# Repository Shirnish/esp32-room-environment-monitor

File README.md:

# ESP32 Room Environment Monitor

I'm building this project as part of my embedded-systems portfolio for Computer Engineering. I started with the Freenove ESP32-S3 kit tutorials and am developing the monitor one version at a time to practice sensor interfacing, debugging, timing, and code organization.

**Current software milestone: V5.1 timed Wi-Fi recovery — October 14, 2026.** I can view temperature, humidity, and motion status from my phone, with the page refreshing every five seconds. The LCD, LEDs, and Serial output still work alongside it. I added a reconnect timer and tested successful recovery twice. I use my router's 2.4 GHz guest network; the original connection rejection is still unexplained, as described in the [Wi-Fi recovery notes](#v51-timed-wi-fi-recovery).

**PCB practice milestone — October 16, 2026:** I also created a routed KiCad carrier-board design. It is an unfabricated layout exercise, separate from the tested breadboard build. [PCB documentation and files](HardWare/room-environment-monitor-v2/ROOM%20ENVIRONMENT%20PCB%20PRACTICE/README.md).

## V1: temperature and humidity over Serial

For V1, I connected a DHT11 sensor and printed temperature in Celsius, temperature in Fahrenheit, and relative humidity to Serial Monitor. I calculate Fahrenheit in the sketch using `(C * 1.8) + 32`.

I use `millis()` to schedule measurement attempts every 2,000 ms. If a reading fails, the program prints the library's error message and waits until the next scheduled attempt before trying again.

I separated the measurement work into `readEnvironment()`. The main `loop()` decides when to call it, while the function reads the sensor, checks its status, calculates Fahrenheit, and prints the results.

## Hardware and wiring

For V1, I used:

- Freenove ESP32-S3 development board and GPIO extension board
- DHT11 temperature/humidity sensor
- 10 kΩ pull-up resistor
- Breadboard, jumper wires, and USB cable

| DHT11 connection | My wiring |
| --- | --- |
| Pin 1: VCC | Board 3.3 V |
| Pin 2: DATA | ESP32-S3 GPIO 21 |
| Pin 3: NC | Unconnected |
| Pin 4: GND | Breadboard ground rail connected to board GND |
| 10 kΩ resistor | Between DATA/GPIO 21 and 3.3 V |

The pull-up resistor holds the data line high when it is idle. Although the tutorial diagram labels the sensor data pin SDA, the DHT11 uses its own digital protocol, not I2C. I don't use an ADC input for this sensor.

Power off before changing wiring, and use the kit's sensor pin diagram to identify the physical pins.

## V1 schematic

[Editable KiCad project](HardWare/room-environment-monitor/room-environment-monitor.kicad_pro) | [PDF schematic](HardWare/room-environment-monitor/room-environment-monitor.pdf)

## Current wiring: V4 schematic

[Editable KiCad project](HardWare/room-environment-monitor-v4/room-environment-monitor-v4.kicad_pro) | [PNG diagram](HardWare/room-environment-monitor-v4/room-environment-monitor-v4.png)

This diagram includes the current GPIO assignments, one 220 ohm resistor per LED, the DHT11 pull-up, the HC-SR501, and the installed LCD voltage interface. V5 adds Wi-Fi and the dashboard without changing the wiring, so this is still the current schematic. I use the module labels to identify connections; the ESP32 board block is a simplified symbol rather than a drawing of the physical headers.

## Software and setup

To run the project:

1. Open `Second_Project.ino` in Arduino IDE. Keep the sketch inside the `Second_Project` folder.
2. Install ESP32 board support, DHTesp, and the kit's LiquidCrystal I2C library. `WiFi` and `WebServer` are included with the ESP32 board package. The LCD communicates through the installed bidirectional level shifter.
3. Copy `secrets.example.h` to `secrets.h` in the sketch folder. Replace the placeholders in `secrets.h` with the name and password of a 2.4 GHz Wi-Fi network. I keep this file local; `.gitignore` excludes it from Git.
4. Select the board configuration and USB port used for the ESP32-S3 kit tutorials.
5. Upload the sketch and open Serial Monitor at **115200 baud**.
6. Check for the startup message, followed by measurements approximately every two seconds. Once Wi-Fi connects, Serial prints `Ip Address:` followed by the assigned address. If it stays disconnected, my retry function prints `Retrying Connection` and starts another attempt when its 30-second interval has elapsed.
7. Connect a phone or computer to the same network and open `http://<printed-IP>/` in a browser, replacing `<printed-IP>` with the actual address. Use HTTP. The page refreshes every five seconds. Guest-network isolation settings can affect whether devices can reach each other; browser access worked on my tested guest network.
8. Allow 60 seconds for PIR warm-up. The backlight stays on and the page says `PIR warming up` during startup. After warm-up, motion and occupancy messages print when their states change, and the backlight follows the occupancy estimate.

Example Serial output:

```text
 Temperature:25.00°C Temperature Fahrenheit:77.00°F Humidity:50.00%
```

This is an example of the output format, not a saved measurement. The installed versions recorded for this milestone are ESP32 board package **3.3.12**, DHTesp **1.19**, and LiquidCrystal I2C **1.1.2**. I still need to record the exact board-menu configuration. The LiquidCrystal I2C library's AVR architecture warning appeared during compilation, but I successfully uploaded and tested the LCD code on my ESP32-S3.

The current sketch runs the DHT11, LCD1602, Serial output, environmental LEDs, PIR motion/occupancy logic, and browser dashboard. I call `readMotion()`, `updateLcdBacklight()`, `checkWifiStatus()`, `wifiConnection()`, and `server.handleClient()` on each loop pass, while `readEnvironment()` stays scheduled every two seconds. The V4 schematic above shows the combined wiring; the earlier schematics remain available as project history.

## V1 testing

I uploaded and tested V1 on my board:

| Test | Result |
| --- | --- |
| Normal sensor readings | Working |
| Celsius, Fahrenheit, and humidity output | Working |
| Refactor into readEnvironment() | Uploaded and working |
| millis() scheduling | Uploaded and working |
| Disconnected DHT11 data wire | Serial printed timeout on the refactored version |

I tested the behavior directly on the hardware. I haven't done sensor accuracy calibration, precise timing measurements, automated build checks, or long-duration testing. I haven't recorded a separate V1 reconnect/recovery test.

To repeat the failure test, power off, disconnect DATA, restart, and check for an error. Power off again before reconnecting DATA, then restart and check that readings return.

## Design decisions and limitations

- I use `millis()` instead of a two-second `delay()` so the program can do other work between measurement attempts.
- I update the attempt timestamp before reading, so failed attempts also respect the interval.
- I use unsigned elapsed-time subtraction to handle millis() rollover.
- I read the sensor inside `readEnvironment()` and save the latest successful measurements in globals for the browser. Opening the page doesn't trigger another sensor read.
- I check the sensor status before converting or printing measurements.
- The sensor transaction still takes time; scheduling with millis() doesn't make the library call asynchronous.
- Printing decimal places doesn't establish the sensor's accuracy or precision.
- I don't store a history of measurements. Failed reads print an error instead of measurements, select the red LED, and replace the LCD readings with an error message. The page hides the saved measurements when `environmentValid` is false, while motion status stays available. The LCD backlight still follows occupancy; sensor errors do not force it on.
- The browser makes a new HTTP request every five seconds. That refresh interval is separate from the two-second sensor interval. Sensor reads, Serial output, I2C operations, and handling a web request can still take time.
- I check Wi-Fi retry timing with `millis()` instead of waiting in a connection loop. My scheduled retry attempts are at least 30 seconds apart. The ESP32 library may also make its own automatic connection attempts.

## V2: LCD development and voltage investigation

I added an I2C LCD1602 while keeping the Serial output. I tested Celsius and Fahrenheit on the first row, humidity on the second, and the messages "Sensor error" and "Check Wiring" when the DHT11 reading fails. My error handler clears both rows before printing its messages. I still need to add padding to normal measurement updates so shorter values fully replace previous text.

I used address **0x27**, SDA on **GPIO 14**, and SCL on **GPIO 13**. Following the Freenove tutorial, I initially powered the LCD from the extension board's USB-supplied **5 V** and connected it to the board's GND.

### V2 schematic: previously tested direct wiring

[Editable V2 direct-wiring KiCad project](HardWare/room-environment-monitor-v2-current/room-environment-monitor-v2-current.kicad_pro) | [PNG diagram](HardWare/room-environment-monitor-v2-current/room-environment-monitor-v2-current.png)

This diagram records the direct 5 V LCD connection I used during functional testing, without a level shifter. I measured the disconnected LCD signal pins near 5 V afterward, so I am documenting this circuit with its unresolved voltage issue rather than treating it as electrically validated. The separate V2 design below shows the level-shifting approach; the current combined V4 schematic is linked above.

### Earlier V2 level-shifter design

[Editable V2 KiCad project](HardWare/room-environment-monitor-v2/room-environment-monitor-v2.kicad_pro) | [PNG diagram](HardWare/room-environment-monitor-v2/room-environment-monitor-v2.png)

I created this diagram while planning the LCD voltage-interface correction. I have since installed the shifter and added the LEDs and PIR. This earlier sheet does not include those additions; the current V4 schematic above documents the combined build.

### Voltage measurements

With the LCD powered at 5 V and its SDA/SCL wires disconnected from the ESP32, I measured approximately **4.9-5.0 V** on those signals relative to GND. I then tried powering the LCD from 3.3 V. The signals measured approximately **3.3 V**, but the display did not show text.

I'm still learning to use the multimeter, so measurement error is possible. I haven't independently verified the readings or checked the meter's accuracy. However, the voltage change followed the module's supply voltage, which is consistent with pull-up resistors connected to that supply. I can't assume the readings are harmless or dismiss them as an error without further testing.

The [ESP32-S3 datasheet, Table 5-4](https://documentation.espressif.com/esp32-s3_datasheet_en.pdf) specifies a high-level input maximum of VDD + 0.3 V, approximately **3.6 V** with a 3.3 V GPIO supply. My measured 5 V signals exceed that specification. Seeing the display work doesn't confirm that the direct connection is electrically compatible.

### Installed LCD interface — October 11, 2026

I installed one module from the [DIYables five-pack of presoldered four-channel bidirectional I2C level shifters](https://diyables.io/products/5-pack-4-channel-iic-i2c-level-converter-module-bi-directional-logic-level-shifter-5v-to-3.3v-for-arduino-raspberry-pi-esp8266-esp32-sensors-presoldered-compact-adapter-board). It translates SDA and SCL between the ESP32's 3.3 V side and the LCD's 5 V side. The LCD still takes power directly from the extension board's USB-supplied 5 V; the shifter does not generate its power.

| Connection | My wiring |
| --- | --- |
| Shifter LV | Board 3.3 V |
| Shifter HV | Board 5 V |
| Shifter GND connections | Board GND |
| LV1 | GPIO 14 / SDA |
| HV1 | LCD SDA |
| LV2 | GPIO 13 / SCL |
| HV2 | LCD SCL |
| LCD VCC | Board 5 V, shared with shifter HV |
| LCD GND | Board GND, shared with all modules |

Channels 3 and 4 are unused. I disconnected USB while changing wiring. Before connecting LV1/LV2 to the ESP32 GPIOs, I powered the shifter and LCD with LCD communication disabled and checked DC voltages relative to common GND:

| Signal | Approximate idle measurement |
| --- | --- |
| LV1 | 3.3 V |
| LV2 | 3.3 V |
| HV1 | 5 V |
| HV2 | 5 V |

I then restored the GPIO connections, LCD initialization, normal measurement display, and sensor-error display calls. The LCD worked alongside Serial output, environmental LEDs, and PIR reporting. With DHT11 DATA disconnected and the board restarted, the LCD showed "Sensor error" / "Check Wiring", the red LED was on, and Serial reported the sensor error. PIR reporting still worked after warm-up. After reconnecting DATA and restarting, normal readings and the appropriate environmental LED returned.

These were manual functional tests and idle DC measurements. I haven't recorded I2C waveforms, independently calibrated the meter, or tested long-duration bus operation. The recovery test used a restart; it does not establish recovery without restarting. I performed these combined sensor-error and recovery tests before adding the backlight control described in V4 below.

The current temperature-row layout is intended for readings below **100 °F**. Higher readings need a shorter layout to fit within the LCD's 16 columns.

## V3: environmental LED status indicators

For this milestone, I added green, yellow, and red LEDs while keeping the DHT11 readings and Serial output. Each LED has its own 220 ohm series resistor. I tested the LEDs individually before connecting their behavior to the sensor readings.

### LED wiring

| LED | ESP32-S3 GPIO | Connection |
| --- | --- | --- |
| Green | 4 | GPIO 4 -> 220 ohm resistor -> anode; cathode -> GND |
| Yellow | 5 | GPIO 5 -> 220 ohm resistor -> anode; cathode -> GND |
| Red | 6 | GPIO 6 -> 220 ohm resistor -> anode; cathode -> GND |

The LEDs and DHT11 share the board's GND. My DHT11 wiring remains the same as V1. I removed the LCD during the original V3 tests; it is now restored in the combined V4 build.

### Status logic

I set the temperature limits to **20-26 degrees Celsius** and the humidity limits to **30-60% relative humidity**. Both endpoints count as within range. These are adjustable project thresholds, not a calibrated assessment of room conditions.

| Sensor result | Green | Yellow | Red |
| --- | --- | --- | --- |
| Valid reading; both measurements within range | ON | OFF | OFF |
| Valid reading; either measurement outside range | OFF | ON | OFF |
| Failed reading | OFF | OFF | ON |

All three LEDs start off until the first measurement attempt. I check the sensor status before comparing measurements, so a failed read selects red instead of being treated as an environmental warning.

I moved the repeated LED writes into `ledControl(bool greenOn, bool yellowOn, bool redOn)`. Its parameters are ordered green, yellow, red. Each status call sets all three outputs, so an LED from the previous status doesn't stay on. `readEnvironment()` still handles the sensor check and range decisions, while `loop()` schedules measurement attempts with `millis()`.

### Hardware testing

I uploaded the sketch and tested these behaviors on my ESP32-S3:

| Test | Result |
| --- | --- |
| Green, yellow, and red LEDs tested individually | Each LED worked; Serial readings continued |
| Within-range reading | Green only |
| Reading outside either configured range | Yellow only |
| Disconnected DHT11 DATA | Red only, with the sensor error in Serial |
| DATA reconnected and board restarted | Normal readings and the appropriate valid-reading indicator returned |
| Refactor into ledControl() | Uploaded and repeated the green, yellow, and red tests successfully |

During testing, a reading of **22.9 degrees Celsius and 64% humidity** selected yellow because humidity exceeded 60%. I temporarily raised `maxHumidity` to 70 to test green, then restored it to 60. Changing the limit let me test the decision without replacing the sensor's measurements with made-up values.

These are manual functional tests. I haven't tested every exact threshold boundary, millis() rollover on hardware, sensor accuracy, or long-duration operation. There is no hysteresis yet, so readings that cross a threshold repeatedly can switch between green and yellow. Reconnecting DATA with a restart verifies recovery after restart; it doesn't establish recovery without restarting.

### Build photos

My ESP32-S3, DHT11, and three status LEDs during V3 testing. The yellow status LED is lit; I had removed the LCD while its level-shifter integration was pending.

A second view of the physical breadboard build. The photos document the assembly; the wiring tables record the GPIO assignments and resistor values.

The LED milestone is complete. I later restored the LCD through the level shifter and tested it with the LEDs and PIR, as recorded in the October 11 integration above.

## V4: PIR motion and occupancy estimate

I added the kit's HC-SR501 PIR motion sensor while keeping the DHT11, Serial output, and environmental LEDs working. I first developed this version with the LCD removed, then restored the display through the level shifter and added occupancy-controlled backlight behavior.

### PIR wiring

| HC-SR501 connection | My wiring |
| --- | --- |
| VCC / + | Extension board's USB-supplied 5 V |
| OUT / S | ESP32-S3 GPIO 7 |
| GND / - | Board GND, shared with the DHT11 and LEDs |

I identify the module pins from their labels and the kit diagram, rather than assuming a left-to-right order. The module uses 5 V power and provides an approximately 3.3 V HIGH output, as described in [Freenove's HC-SR501 documentation](https://docs.freenove.com/projects/fnk0082/en/latest/fnk0082/codes/Python/25_Infrared_Motion_Sensor.html). I read OUT with `digitalRead()`; the PIR needs no additional library or ADC conversion.

### Timing and state logic

| Setting | Current value | Purpose |
| --- | --- | --- |
| `readInterval` | 2,000 ms | Schedule DHT11 measurement attempts |
| `pirWarmupInterval` | 60,000 ms | Suppress PIR and occupancy reporting during startup |
| `occupancyTimeout` | 15,000 ms | Keep the occupancy estimate true after the last sampled HIGH |

I set `pirStartTime` in `setup()`. During warm-up, `readMotion()` returns immediately, so temperature, humidity, and LED updates continue without a 60-second `delay()`.

I call `readMotion()` on each pass through `loop()`, outside the two-second DHT timing condition. Motion polling is independent of that interval, although a sensor transaction or Serial output can still take time. This is polling, not interrupt-based event capture.

`previousMotionState` starts at -1 so the first PIR reading after warm-up prints once. Later, I print `PIR: 0` or `PIR: 1` only when the level changes.

When the PIR is HIGH, I set `occupied` to true and refresh `lastMotionTime` on every HIGH reading. When it is LOW, I keep the previous occupancy estimate until 15 seconds have elapsed since the last sampled HIGH. New HIGH readings refresh the timer. I capture the old occupancy value before updating it, then print an occupancy message only if the value changed.

An illustrative sequence of motion messages is:

```text
PIR: 1
Occupancy: Occupied
PIR: 0
Occupancy: No Recent Movement
```

The last line appears after the software timeout; it is not printed immediately with `PIR: 0`. Temperature and humidity messages continue between these events. This example shows the format, not a captured Serial log. If the first PIR reading is LOW, only `PIR: 0` prints initially because `occupied` already starts false.

### Hardware testing

I uploaded and tested the motion and occupancy behavior on my ESP32-S3:

| Test | Result |
| --- | --- |
| PIR motion and return to LOW | Both 1 and 0 observed |
| `readMotion()` refactor and motion-change reporting | Working; PIR messages print on level changes |
| 60-second warm-up | Environmental readings and LEDs continue; PIR reporting begins after warm-up |
| HIGH after warm-up | Occupancy becomes true and prints once |
| LOW before the software timeout | Occupancy stays true |
| LOW through the 15-second software timeout | Occupancy clears and prints once |
| HIGH returns before the timeout expires | Timer refreshes and occupancy stays true |

During the earlier raw-input test, I estimated that the PIR took about 40-60 seconds to return LOW after activity. I did not time that precisely. The module's own hold time and my software timeout are separate: the software keeps occupancy true for about 15 seconds after the output goes LOW. I haven't recorded the potentiometer positions or H/L jumper setting yet.

### Occupancy-controlled LCD backlight

I added `updateLcdBacklight()` and call it immediately after `readMotion()`. The backlight starts on and stays on during the 60-second PIR warm-up. After warm-up, it follows `occupied`: recent activity turns it on, and the occupancy timeout turns it off. If the first PIR reading after warm-up is LOW and no activity has been recorded, it turns off at that point.

I track the commanded backlight state in `lcdBacklightOn` and send `lcd.backlight()` or `lcd.noBacklight()` only when the desired state changes. Turning off the backlight leaves the LCD powered. Measurement display updates, Serial output, environmental LEDs, and motion polling continue.

I uploaded this version and tested:

| Test | Result |
| --- | --- |
| Startup warm-up | Backlight stays on |
| LOW after warm-up with no recorded activity | Backlight turns off |
| PIR HIGH / occupied | Backlight turns on |
| PIR returns LOW | Backlight remains on during the occupancy grace period |
| LOW continues through the occupancy timeout | Backlight turns off |
| Backlight off | Serial readings and environmental LEDs continue working |

The backlight follows occupancy even during a DHT11 error. Error text is still written to the LCD, but the code does not force illumination on; Serial and the red LED remain the other error indicators. The final hardware photos below show normal operation and the LCD/red-LED response to a disconnected DHT data wire on the current build.

### Current build photos

My combined V4 assembly with the PIR held above the breadboard and the LCD connected alongside it. The breadboard includes the DHT11, level shifter, and three environmental status LEDs.

A closer view of my DHT11, installed level shifter, and LED wiring. These photos document the physical assembly; they do not show active LCD readings. My functional test results are recorded in the tables above.

### Limitations and next steps

This is an occupancy estimate based on recent PIR activity. A stationary person may stop triggering the sensor, so I use the message "No Recent Movement" instead of claiming that the room is empty. A LOW reading also doesn't distinguish no activity from a disconnected or failed PIR signal.

These are manual functional tests. I haven't measured response latency, checked long-duration operation or millis() rollover on hardware, or calibrated detection coverage. PIR reporting is suppressed during warm-up, so startup should not be interpreted as a confirmed empty-room state.

The combined V4 motion/occupancy, LCD, and backlight milestone is complete. The updated KiCad diagram above includes the PIR, LEDs, and installed level shifter. The current build photos are included above, and the earlier V3 photos remain labeled as V3.

## V5: Wi-Fi and browser dashboard

I started by connecting the ESP32 to Wi-Fi and printing its IP address in Serial Monitor. I then added a simple web response and opened it on my phone. Once that worked, I added the readings, sensor-error handling, motion status, an HTML heading, and automatic refresh.

My V5 dashboard displaying 22.0 C, 71.6 F, 64.2% humidity, and an occupied status. This image records the page during testing; the values come from the saved sensor readings and motion state.

The page currently shows:

- Temperature in Celsius and Fahrenheit
- Relative humidity
- `Sensor Reading Unavailable` if the DHT reading fails or no successful reading has happened yet
- `PIR warming up`, `Occupancy: Occupied`, or `Occupancy: No recent Movement`

The ESP32 serves the page at `/` on port 80. I build the response in `handleRoot()` and send it once with `server.send()`. The page uses a five-second HTML refresh setting, so I don't need to reload it manually.

### Saved readings and separate state

I keep the latest successful measurements in `latestTemperatureC`, `latestTemperatureF`, and `latestHumidity`. `environmentValid` starts false, becomes true after a successful read, and goes false after a failed read. The saved numbers remain in memory after a failure, but the page shows the error message instead of presenting them as current readings.

The browser uses these saved values. `readEnvironment()` still controls when the DHT is read, so opening or refreshing the page doesn't request another measurement. I add motion status separately from the environmental `if/else`, so a DHT error doesn't hide occupancy information. During PIR warm-up, I show the warm-up message instead of treating the initial false occupancy value as no recent movement.

### What I tested

I uploaded each addition and checked it on my ESP32-S3 and phone:

| Test | Result |
| --- | --- |
| Connect to the 2.4 GHz guest network | Connected and received an IP address |
| Open the printed HTTP address on my phone | Displayed `Room Monitor Online` in the first test |
| Add the saved Celsius, Fahrenheit, and humidity readings | Displayed the measurements |
| Failed DHT reading | Page displayed the unavailable message |
| Add PIR warm-up and occupancy reporting | Page displayed motion status separately from the measurements |
| Convert the response to HTML | Heading and measurement lines displayed correctly |
| Add the five-second refresh setting | Page refreshed without manually reloading |

These were manual functional tests. I haven't measured request latency, tested multiple browsers at once, or run a long-duration test. The V5.1 section below records the reconnect changes and two successful recovery tests.

### Wi-Fi connection investigation

I tested with a NETGEAR Nighthawk RAX50. Attempts on my main network reported reason `201` (`NO_AP_FOUND`). Separating the 2.4 GHz network from Smart Connect didn't resolve it. Using the 2.4 GHz guest network did let the ESP32 connect, and I could access the page from my phone.

During reset and USB disconnect/reconnect testing, some connection attempts failed. Serial showed `Association refused too many times, max allowed 1`, reason `208` (`ASSOC_COMEBACK_TIME_TOO_LONG`), and reason `36` (`STA_LEAVING`). I haven't confirmed the cause. The [Espressif reason-code documentation](https://docs.espressif.com/projects/esp-idf/en/stable/esp32s3/api-guides/wifi-driver/station-scenarios.html) describes reason 208 as an association response with a comeback time that is too long.

I kept the disconnect callback to print the reason codes. My application starts the initial connection in `setup()` and reports connection changes in `checkWifiStatus()`. I then added the timed retry function below to recover from failures instead of relying on another manual reset.

## V5.1: timed Wi-Fi recovery

I added `wifiConnection()` and call it from `loop()`, outside the two-second sensor timing block. It checks whether Wi-Fi is disconnected and whether at least `wifiRetryInterval` (30,000 ms) has passed since my previous attempt. If both are true, it updates `lastWifiAttemptTime`, prints `Retrying Connection`, and calls `WiFi.reconnect()`.

I set the timestamp before the first `WiFi.begin()` call too. Updating it before each retry keeps unsuccessful attempts from being repeated on every loop pass. The function has no waiting loop or `delay()`. `WiFi.reconnect()` starts an attempt; `checkWifiStatus()` reports the IP and starts the web server when a connection is established.

| Test | Result |
| --- | --- |
| New timed reconnect code | ESP32 reconnected successfully in two manual tests |

The two successful recoveries show that the new retry code can recover in my tested setup. I haven't recorded recovery times, the reason code for each test, a larger reset test series, or a separate network-outage recovery test. The original association rejection is still unexplained, so I am documenting recovery rather than claiming that the underlying router issue is fixed.

## Final hardware demonstration

I used photos to document the finished breadboard build alongside the dashboard image above.

The LCD shows 22.2 C, 72.0 F, and 65.8% humidity. Temperature is within my configured 20-26 C range, but humidity is above the 60% upper limit, so the yellow LED is on. The reading is valid; yellow means a measurement is outside my project limits.

I disconnected the DHT data wire to test a failed reading. The LCD shows `Sensor error` and `Check Wiring`, and the red LED is on. This is the sensor-failure state, separate from the yellow environmental warning.

| Photo | What I demonstrated |
| --- | --- |
| Normal readings with yellow LED | Valid measurements, with humidity outside the configured range |
| DHT DATA disconnected with red LED | Failed sensor reading and LCD error message |

These photos record the LCD and LED states. The dashboard image and manual test results are documented separately above.

### Remaining breadboard improvements

This completes the planned breadboard build and its photo documentation. I also used the circuit as the basis for the separate PCB practice exercise below. The breadboard tests do not establish that the PCB works.

Other possible improvements are investigating the original Wi-Fi rejection, a phone-friendly page layout, and padding normal LCD updates so shorter readings clear the previous text.

## PCB practice: KiCad carrier board

I made a two-layer carrier-board layout to practice schematic-to-PCB work in KiCad. It uses the Freenove ESP32-S3 development board directly in two socket rows, without the GPIO extension board. The DHT11, LED resistors, level-shifter sockets, and external LCD/PIR connectors follow the room monitor's signal assignments.

**This is an unfabricated design exercise.** I have not ordered, assembled, or tested this PCB. The plug-in ESP32 and level-shifter modules are represented by sockets in the rendering; the generic LED models all appear red.

Fresh checks in KiCad CLI **10.0.6 on October 16, 2026** reported **0 ERC errors/warnings, 0 DRC errors/warnings, 0 unconnected PCB items, and 0 schematic-parity issues**, under the saved project's enabled checks. Module fit and the provisional level-shifter row spacing remain unverified.

[PCB design notes, pin mapping, limitations, and editable files](HardWare/room-environment-monitor-v2/ROOM%20ENVIRONMENT%20PCB%20PRACTICE/README.md) · [PCB layout screenshot](docs/images/pcb-practice/pcb-layout.png) · [Schematic screenshot](docs/images/pcb-practice/schematic.png)

The PCB notes explain the front ground pour, routing on both copper layers, the LCD-ground thermal-relief correction, dimension sources, and the guided workflow. They also link the fresh check reports and input hashes.

## Version progression

- **V1:** DHT11 to Serial Monitor — completed and hardware tested as described above
- **V2:** LCD1602 output — restored through the level shifter; idle voltages and combined functional tests recorded above
- **V3:** Environmental LED status indicators — completed and hardware tested; working with the restored LCD
- **V4:** PIR motion/occupancy estimate and LCD backlight control — completed and hardware tested as described above
- **V5:** Wi-Fi and a browser dashboard — dashboard tested on my phone
- **V5.1:** Timed Wi-Fi recovery — reconnected successfully in two manual tests; original rejection cause remains unconfirmed

V5 and V5.1 use the V4 wiring and assembly photos above. The V5 dashboard image and final LCD/LED demonstration photos document the working breadboard build. The separate PCB practice design is routed and checked in KiCad, but has not been fabricated or hardware tested.

## References and attribution

I used the **Freenove ESP32-S3 Ultimate Starter Kit tutorial** as the starting point for the sensor code and wiring. The tutorial schematic was a reference; I haven't redistributed it in this repository.

My changes include calculating Fahrenheit, replacing the goto retry loop with error reporting, using millis() scheduling, separating the work into functions, adding LCD measurements and error messages, selecting LED status indicators from sensor validity and configurable thresholds, adding PIR state-change reporting with a non-blocking warm-up and occupancy timeout, installing I2C level shifting, controlling the LCD backlight from the occupancy estimate, serving saved readings and motion status in a browser, and adding timed Wi-Fi retries.

Libraries:

- [DHTesp](https://github.com/beegee-tokyo/DHTesp)
- [LiquidCrystal I2C](https://github.com/marcoschwartz/LiquidCrystal_I2C)
- [Arduino-ESP32](https://github.com/espressif/arduino-esp32) — board support, WiFi, and WebServer

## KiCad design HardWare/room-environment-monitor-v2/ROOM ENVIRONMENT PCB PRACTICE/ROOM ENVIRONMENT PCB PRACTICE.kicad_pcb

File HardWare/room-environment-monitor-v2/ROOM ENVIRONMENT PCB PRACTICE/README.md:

# Room Monitor — KiCad PCB Practice

I made this carrier-board layout to practice moving from a schematic to a routed PCB in KiCad. It uses the DHT11, LEDs, PIR connector, LCD connector, and I2C level-shifter interface from my room monitor.

**Status — October 16, 2026:** schematic and PCB checks pass under the saved project settings. This is an **unfabricated design exercise**. I have not ordered, assembled, powered, or physically tested this PCB. The working breadboard build and its tests are documented in the [main project README](../../../README.md).

This is a KiCad rendering, not a photograph of an assembled PCB. The ESP32-S3 and level-shifter modules are represented by their sockets. The LCD and PIR are external modules connected through J1 and J2. All three LEDs look red because they share a generic 3D model; the schematic and silkscreen identify their intended colors.

## Project files

Open [ROOM ENVIRONMENT PCB PRACTICE.kicad_pro](<ROOM ENVIRONMENT PCB PRACTICE.kicad_pro>) in **KiCad 10.0.6**, then open its schematic or PCB. Keep the following files together:

| File | Purpose |
| --- | --- |
| [Schematic](<ROOM ENVIRONMENT PCB PRACTICE.kicad_sch>) | Connections and assigned footprints |
| [PCB layout](<ROOM ENVIRONMENT PCB PRACTICE.kicad_pcb>) | Placement, routing, outline, ground zone, and silkscreen |
| [Project settings](<ROOM ENVIRONMENT PCB PRACTICE.kicad_pro>) | Saved rules and project configuration |
| [RoomMonitor.kicad_sym](RoomMonitor.kicad_sym) and [sym-lib-table](sym-lib-table) | Local symbols and their project-relative library registration |
| [ERC report](ERC.rpt) / [ERC JSON](validation/erc.json) | Fresh schematic-check results |
| [DRC report](validation/DRC.rpt) / [DRC JSON](validation/drc.json) | PCB-check, connectivity, and schematic-parity results |
| [Validation manifest](validation/manifest.json) | Check date, options, and SHA-256 hashes of the checked inputs, with text line endings normalized to LF |

The footprints use KiCad's standard libraries. Install the standard symbol and footprint libraries when opening the project on another computer; the 3D models also depend on the corresponding KiCad model libraries. The folder is under `room-environment-monitor-v2` for historical reasons; this practice layout includes the later LEDs, PIR, and level-shifted LCD connections.

## What the board represents

| Reference | Part or connection |
| --- | --- |
| J5 / J6 | Two 20-position sockets for the Freenove ESP32-S3 development board, used directly without its GPIO extension board |
| U2 / R4 | Bare four-pin DHT11 and its 10 kΩ data pull-up to 3.3 V |
| D3 / R1 | Green LED and 220 Ω series resistor, controlled by GPIO4 |
| D2 / R2 | Yellow LED and 220 Ω series resistor, controlled by GPIO5 |
| D1 / R3 | Red LED and 220 Ω series resistor, controlled by GPIO6 |
| J2 | Three-pin cable connector for the HC-SR501 PIR, with OUT connected to GPIO7 |
| J3 / J4 | The LV and HV socket rows of one plug-in, four-channel level-shifter module |
| J1 | Four-pin cable connector for the external I2C LCD1602 |

This carrier assumes the ESP32 development board provides USB-derived 5 V and regulated 3.3 V through its headers. I did not add a separate USB connector, regulator, or power-selection circuit to the carrier.

### Connector pin order

These orders refer to the **top view of this PCB**, matching the silkscreen. J2 is rotated, so its numbering runs in the opposite direction from J1.

| Connector | Top-to-bottom pad numbers | Top-to-bottom signals |
| --- | --- | --- |
| J1 — LCD | 1, 2, 3, 4 | GND, 5 V, SDA, SCL |
| J2 — PIR | 3, 2, 1 | GND, OUT, 5 V |
| J3 — LV | 1, 2, 3, 4, 5, 6 | LV1/SDA, LV2/SCL, 3.3 V, GND, LV3 unused, LV4 unused |
| J4 — HV | 1, 2, 3, 4, 5, 6 | HV1/SDA, HV2/SCL, 5 V, GND, HV3 unused, HV4 unused |

The cable wiring must match the actual LCD and PIR module labels. These connector orders are the carrier's assignments, not a claim that every module sold with the same name has the same physical pin order.

### Signal and voltage connections

| Function | PCB connection |
| --- | --- |
| DHT11 data | U2 pin 2 and R4 pin 2 → J6 pin 17 / GPIO21 |
| DHT11 supply | U2 pin 1 and R4 pin 1 → 3.3 V |
| DHT11 unused pin | U2 pin 3 remains unconnected |
| Green / yellow / red control | R1 / R2 / R3 pin 1 → J5 pins 3 / 4 / 5, respectively |
| PIR OUT | J2 pin 2 → J5 pin 6 / GPIO7 |
| I2C SDA, low-voltage side | J5 pin 19 / GPIO14 → J3 pin 1 |
| I2C SCL, low-voltage side | J5 pin 18 / GPIO13 → J3 pin 2 |
| I2C SDA, high-voltage side | J4 pin 1 → J1 pin 3 |
| I2C SCL, high-voltage side | J4 pin 2 → J1 pin 4 |
| 3.3 V distribution | J5 pin 1 → J3 pin 3, U2 pin 1, and R4 pin 1 |
| 5 V distribution | J5 pin 20 → J2 pin 1, J4 pin 3, and J1 pin 2 |
| Common ground | J6 pin 20, U2 pin 4, LED cathodes, J1 pin 1, J2 pin 3, and J3/J4 pin 4 |

The level-shifter module translates SDA and SCL internally. I did not route a direct copper connection between its LV and HV signal pins. Its HV reference and the LCD supply use 5 V; its LV reference and the ESP32 GPIO side use 3.3 V.

## Schematic and layout

[Zoomable schematic SVG export](../../../docs/images/pcb-practice/schematic.svg)

The schematic represents the two physical ESP32 header rows, while the earlier V4 wiring diagram in the main README uses a simplified board block. `PWR_FLAG` symbols tell ERC which power nets have a source; they do not create a supply or regulate voltage.

The saved layout has **two copper layers, 14 footprints, 77 pads, 64 track segments, no vias, and one front-layer GND zone**. The current tracks are 0.20 mm wide. I used through-hole pads to connect tracks on either side without adding separate vias. These are the current practice-design settings, not a measured current-capacity or thermal result.

I placed all components on the front. The board outline has a **79 × 60 mm bounding size**, with a notch at the ESP32 antenna end. I aimed for about 3 mm between the outermost component courtyards and the outside board edge; that was a placement guide around the whole arrangement, not a required 3 mm gap between every component. The antenna notch is a separate clearance feature, and I have not verified RF performance.

The front GND pour connects the LCD, PIR, LED cathodes, DHT11, and level-shifter grounds back to J6 pin 20. Thermal reliefs connect ground pads to the pour. Other nets are separated from it by clearance gaps.

### Back-copper routing

This export shows **B.Cu viewed from the front**, with front silkscreen included to identify components. It is not a mirrored bottom view. It makes the back tracks easier to inspect than the solder-mask-covered underside rendering.

[Front-copper export](../../../docs/images/pcb-practice/pcb-front-copper.svg) · [Back-layer-highlighted editor screenshot](../../../docs/images/pcb-practice/pcb-back-highlighted.png) · [Underside 3D rendering](../../../docs/images/pcb-practice/pcb-3d-back.png)

## Checks and a routing correction

I checked the saved files with **KiCad CLI 10.0.6 on October 16, 2026**:

| Check | Result |
| --- | --- |
| Schematic ERC | 0 errors, 0 warnings |
| PCB DRC after refilling zones | 0 errors, 0 warnings |
| Unconnected PCB items | 0 |
| PCB-to-schematic parity | 0 issues |

These screenshots show the GUI results. Both zone refill and schematic-parity testing were enabled for the DRC screenshot. The saved JSON reports also record which checks were ignored.

The JSON reports list the project's `ignored_checks`. These results apply to the **enabled project checks**; they do not mean every available KiCad rule was enabled. ERC/DRC also do not establish that the modules fit, that the circuit works on a fabricated board, or that the antenna clearance is sufficient.

One useful correction came after filling the GND zone. The LCD clock track originally ran on F.Cu beside J1 and blocked the pour's thermal connection to J1 pad 1. Moving that clock connection to B.Cu, outside the existing 5 V route, gave the ground pour room to connect. I refilled the zone and checked connectivity again. I also moved the U2 reference text away from R4's pad to clear a silkscreen warning.

To repeat the checks, run these commands from this project folder with `kicad-cli` available on your PATH:

```powershell
kicad-cli sch erc --format json --exit-code-violations --output validation/erc.json "ROOM ENVIRONMENT PCB PRACTICE.kicad_sch"
kicad-cli pcb drc --schematic-parity --refill-zones --format json --exit-code-violations --output validation/drc.json "ROOM ENVIRONMENT PCB PRACTICE.kicad_pcb"
```

The DRC command refills zones for the check without saving the board. In the PCB Editor, I use **B** to refill zones before saving. The [validation manifest](validation/manifest.json) identifies the inputs used for the recorded results. Its hashes normalize text line endings to LF so Windows and Unix checkouts can be compared; rerun the checks after editing the inputs.

## Dimensions and limits of this exercise

| Item | Basis and remaining uncertainty |
| --- | --- |
| ESP32 socket-row spacing: 25.4 mm | Based on a Freenove mechanical drawing publicly shared in the [TF-Luna Security System journal](https://blueprint.hackclub.com/projects/7234), under “Updated Freenove ESP32-S3 Header.” The author says Freenove supplied the drawing. I have not independently measured or fitted my board. |
| ESP32 development-board body | That drawing labels the body 27.94 × 50.8 mm, with an antenna projection beyond it. The carrier uses the development board directly, without the extension board. |
| Level-shifter socket-row spacing: 10.16 mm | A provisional assumption for the DIYables module. I have not verified this distance against a manufacturer mechanical drawing or a physical fit. |
| Connector pitch: 2.54 mm | Pitch of the assigned standard KiCad header/socket footprints. Actual mating parts and their orientation still need verification. |
| LEDs and resistors | Assigned 5 mm LED footprints and axial resistor footprints with 7.62 mm lead spacing. I selected them for the kit parts, but have not measured the actual packages or fitted them to a board. |

The notch and socket placement are a layout exercise, not a complete mechanical model of the plug-in modules. USB access, module overhang, socket height, DHT11 clearance, temperature effects from the ESP32, and antenna behavior remain untested. I am not ordering this revision or presenting it as fabrication-ready.

## What I practiced

I placed components, routed signal and power tracks, added the ground zone, and added the title and revision in KiCad while working through guided reviews. I used AI assistance for the board outline, some silkscreen edits, checking the saved files, and preparing this documentation.

The main lessons were matching symbol pins to footprint pads, distinguishing footprint mounting side from routing layer, keeping the two level-shifter voltage domains separate, connecting grounds through a copper pour, and using ERC/DRC results to correct specific problems. The working breadboard tests belong to the main project; this PCB adds layout practice rather than another hardware-tested version.

## References

- [Freenove ESP32-S3 board repository](https://github.com/Freenove/Freenove_ESP32_S3_WROOM_Board) — board documentation and pinout context.
- [TF-Luna Security System journal](https://blueprint.hackclub.com/projects/7234) — public Freenove measurement drawing in the December 25, 2025 header-update entry. I used the dimension reference, not the other project's circuit or footprint file.
- [DIYables presoldered level-shifter product](https://diyables.io/products/5-pack-4-channel-iic-i2c-level-converter-module-bi-directional-logic-level-shifter-5v-to-3.3v-for-arduino-raspberry-pi-esp8266-esp32-sensors-presoldered-compact-adapter-board) — identifies the module used in the breadboard build; it does not verify the provisional socket-row spacing above.
- [KiCad 10 PCB Editor manual](https://docs.kicad.org/10.0/en/pcbnew/pcbnew.html) — routing, zones, silkscreen, and DRC workflow.

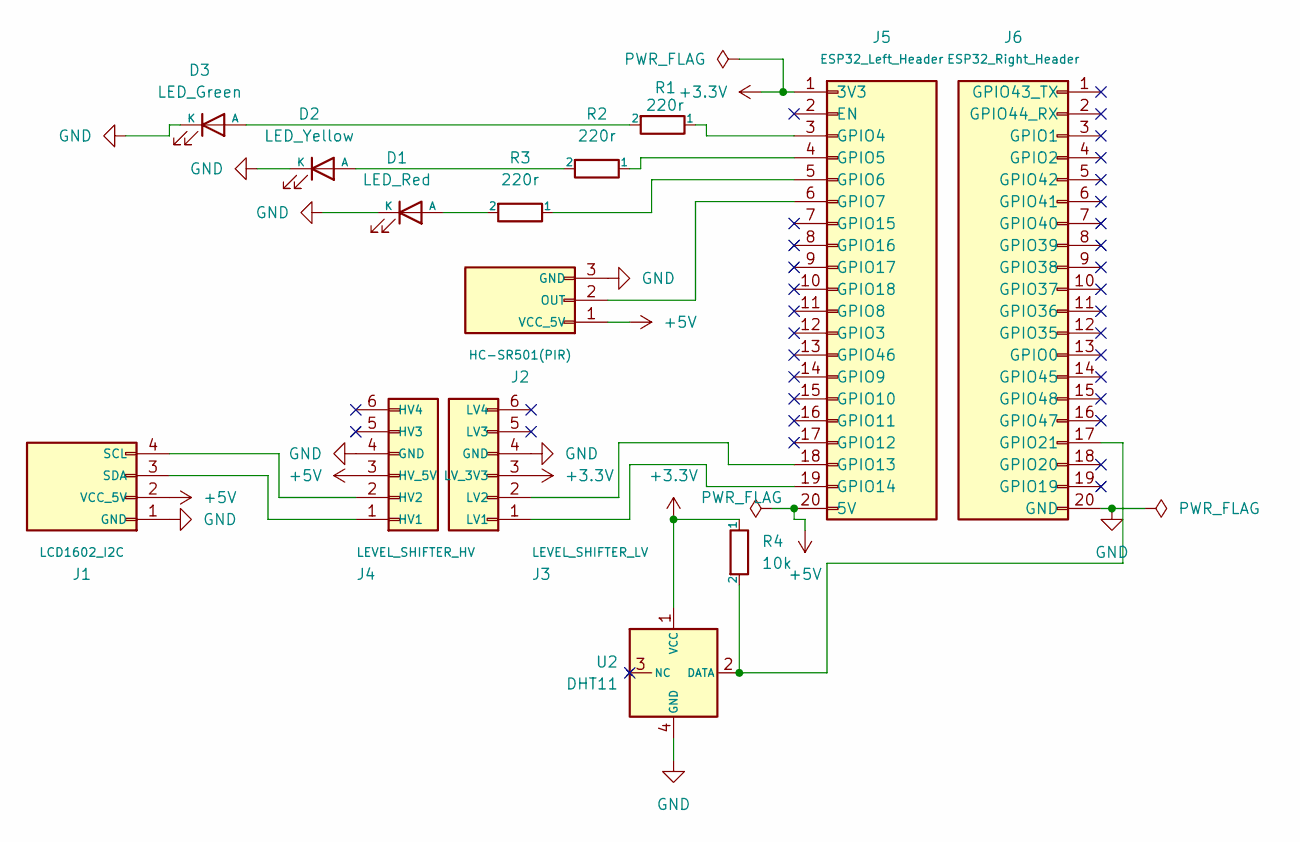
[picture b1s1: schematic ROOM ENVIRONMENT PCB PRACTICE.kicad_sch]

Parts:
D1: LED_Red; LED_D5.0mm
D2: LED_Yellow; LED_D5.0mm
D3: LED_Green; LED_D5.0mm
J1: LCD1602_I2C; PinHeader_1x04_P2.54mm_Vertical
J2: HC-SR501(PIR); PinHeader_1x03_P2.54mm_Vertical
J3: LEVEL_SHIFTER_LV; PinSocket_1x06_P2.54mm_Vertical
J4: LEVEL_SHIFTER_HV; PinSocket_1x06_P2.54mm_Vertical
J5: ESP32_Left_Header; PinSocket_1x20_P2.54mm_Vertical
J6: ESP32_Right_Header; PinSocket_1x20_P2.54mm_Vertical
R1, R2, R3: 220r; R_Axial_DIN0207_L6.3mm_D2.5mm_P7.62mm_Horizontal
R4: 10k; R_Axial_DIN0207_L6.3mm_D2.5mm_P7.62mm_Horizontal
U2: DHT11; Aosong_DHT11_5.5x12.0_P2.54mm

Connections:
+3.3V: J3.3 (LV_3V3), J5.1 (3V3), R4.1, U2.1 (VCC)
+5V: J1.2 (VCC_5V), J2.1 (VCC_5V), J4.3 (HV_5V), J5.20 (5V)
GND: D1.1 (K), D2.1 (K), D3.1 (K), J1.1 (GND), J2.3 (GND), J3.4 (GND), J4.4 (GND), J6.20 (GND), U2.4 (GND)
unnamed: D1.2 (A), R3.2
unnamed: D2.2 (A), R2.2
unnamed: D3.2 (A), R1.2
unnamed: J1.4 (SCL), J4.2 (HV2)
unnamed: J1.3 (SDA), J4.1 (HV1)
unnamed: J2.2 (OUT), J5.6 (GPIO7)
unnamed: J3.1 (LV1), J5.19 (GPIO14)
unnamed: J3.2 (LV2), J5.18 (GPIO13)
unnamed: J5.3 (GPIO4), R1.1
unnamed: J5.4 (GPIO5), R2.1
unnamed: J5.5 (GPIO6), R3.1
unnamed: J6.17 (GPIO21), R4.2, U2.2 (DATA)

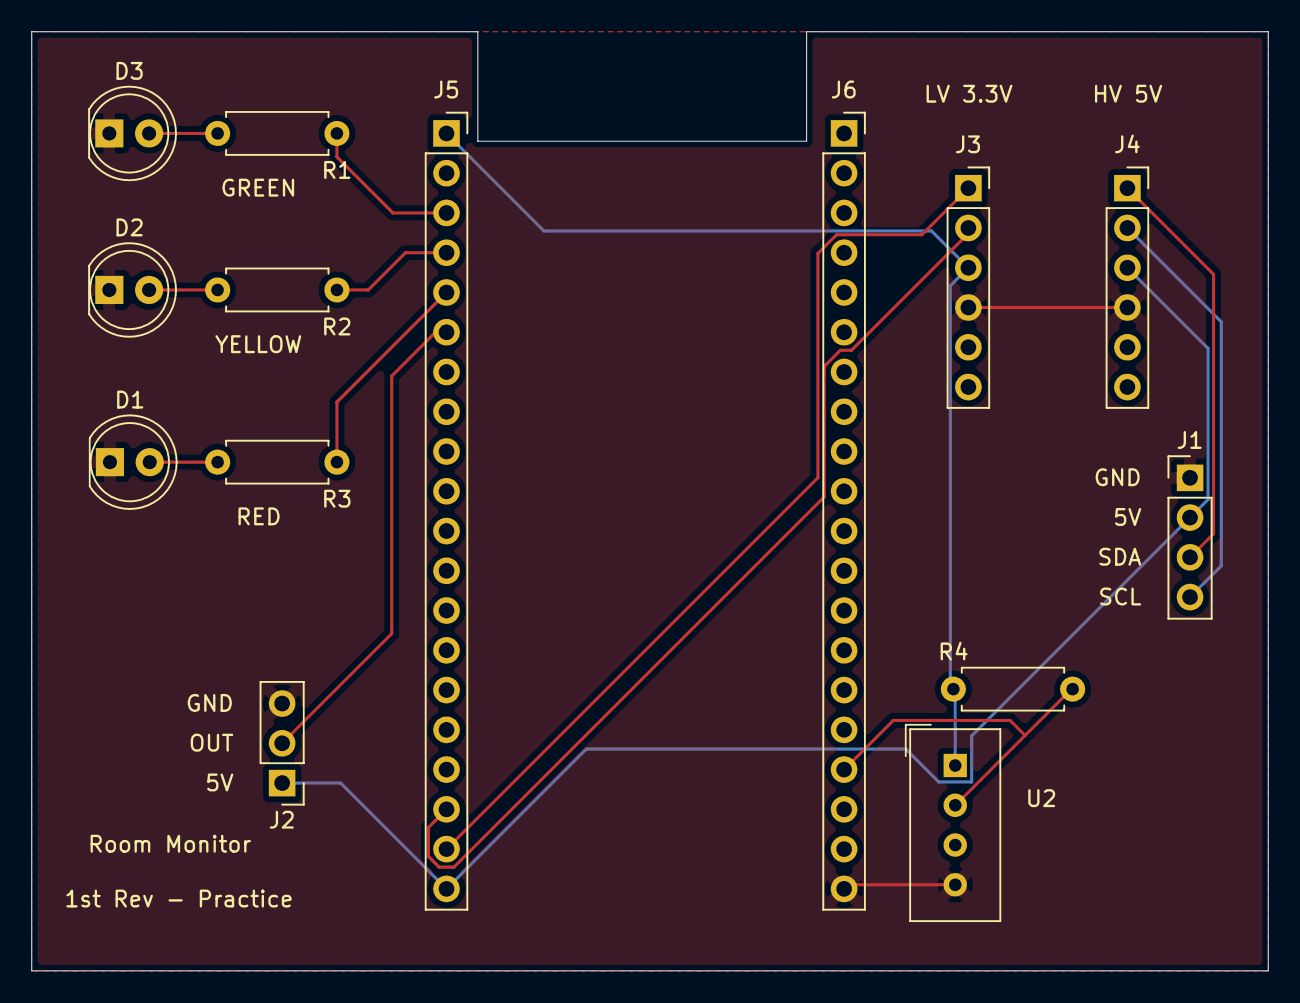
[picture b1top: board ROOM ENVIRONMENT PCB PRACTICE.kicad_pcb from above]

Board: 2 copper layers, 79.0 x 60.0 mm, 14 parts (0 on the bottom side), 15 nets.
